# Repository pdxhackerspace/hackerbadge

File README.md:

# PDX Hackerspace Hackerbadge

The unofficial badge of PDX Hackerspace.

- 37 WS2812B addressable RGB LEDs
- SeeedStudio Xiao ESP32-S3 (8MB PSRAM/8MB flash)
- LSM6DSO accelerometer/gyroscope
- 18650 LiPO battery
- Qwiic/STEMMA QT I2C connector

Though we've specced this for a Xiao ESP32-S3, this should work with any Xiao board with a compatible pinout. If the board doesn't support LiPO battery charging then obviously it will only work when plugged into USB.

## LED power

LEDs are powered either through the VBUS or VBAT, avoiding straining the board's 3.3V regulator and providing more voltage to them for more reliable operation. We use two SS23 Schottky diodes to OR the power sources together and avoid feeding back into one another.

## LED control

Xiao ESP32-S3 D10 controls the LEDs.

## Qwiic/STEMMA QT/I2C

SDA - D1
SCL - D0

## Accelerometer/Gyroscope

The board includes an LSM6DSO accelerometer/gyroscope for fancy effects, or you can just ignore it. I2C address 0x6A.

## Firmware

Hardware self-test sketches live under `firmware/test/`. They cycle LED colors/patterns and exercise the LSM6DSO. Production-style options (WLED, ESPHome, CircuitPython) are below.

### WLED

1. Hold the Xiao **BOOT** button, plug in USB, then release BOOT so the board is in download mode.
2. Open the [WLED web installer](https://install.wled.me/) (or [alternate installer](https://wled-install.github.io/)) in Chrome/Edge.
3. Choose an **ESP32-S3** build that matches this board: **8MB flash** and **PSRAM** (OPI / `qio_opi` style binaries are the usual fit for the Xiao ESP32-S3). Flash it.
4. Join Wi‑Fi AP `WLED-AP` (password `wled1234`) and open [http://4.3.2.1](http://4.3.2.1).
5. **Config → LED Preferences** and set:
   - LED count / length: **37**
   - GPIO / data pin: **9** (Xiao **D10**)
   - LED type: **WS281x**
   - Color order: **GRB**
6. Save, then optionally configure your home Wi‑Fi under **Config → WiFi Setup**.

Stock WLED does not use the LSM6DSO.

**Docker Compose** (build a badge-tuned binary with GPIO 9 / 37 LEDs preconfigured):

```bash
cd firmware/wled
docker compose run --rm build
```

Firmware ends up under `firmware/wled/build/`. Flash with the web installer, `esptool`, or:

```bash
DEVICE=/dev/ttyACM0 docker compose run --rm --device=$DEVICE build upload
```

If the OPI-PSRAM build won’t boot, try `PIO_ENV=hackerbadge_qspi docker compose run --rm build`. See also [Compiling WLED](https://kno.wled.ge/advanced/compiling-wled/).

### ESPHome

Test config: `firmware/test/esphome/badge_test.yaml`

Requires an ESPHome release with the `motion` / `lsm6ds` platform. After flash, the badge cycles LED effects and logs IMU samples over serial. It also brings up AP `Hackerbadge-Test` (password `hackerspace`); open [http://192.168.4.1](http://192.168.4.1) for the web UI.

**Docker Compose** (dashboard on [http://localhost:6052](http://localhost:6052)):

```bash
cd firmware/test/esphome
docker compose up
```

Compile only, or compile and flash over USB:

```bash
docker compose run --rm esphome compile badge_test.yaml
DEVICE=/dev/ttyACM0 docker compose run --rm --device=$DEVICE esphome run badge_test.yaml
```

Without Docker: `esphome run firmware/test/esphome/badge_test.yaml`

### CircuitPython

Test program: `firmware/test/circuitpython/code.py`

1. Install [CircuitPython for Seeed Xiao ESP32-S3](https://circuitpython.org/board/seeed_xiao_esp32s3/).
2. From the [Adafruit library bundle](https://circuitpython.org/libraries), copy into `CIRCUITPY/lib/`:
   - `neopixel.mpy` (and `adafruit_pixelbuf.mpy` if present in your bundle)
   - `adafruit_lsm6ds/`
   - `adafruit_bus_device/`
   - `adafruit_register/`
3. Copy `firmware/test/circuitpython/code.py` to `CIRCUITPY/code.py`.

Watch the serial REPL for IMU logs while LEDs cycle.

### Arduino

Test sketch: `firmware/test/arduino/badge_test/badge_test.ino`

**Docker Compose** (Arduino CLI build; artifacts in `firmware/test/arduino/build/`):

```bash
cd firmware/test/arduino
docker compose run --rm build
```

Upload over USB after a successful compile:

```bash
DEVICE=/dev/ttyACM0 docker compose run --rm --device=$DEVICE build upload
```

Without Docker:

1. In Arduino IDE, install board support for **Seeed XIAO ESP32S3**.
2. Install libraries: **FastLED**, **Adafruit LSM6DS** (pulls in BusIO and Unified Sensor).
3. Open the `badge_test` sketch, select the Xiao ESP32S3 board/port, and upload.

Serial Monitor at 115200 baud shows effect names and IMU readings.

## Assembly

The badge comes prebuilt except for the Xiao and the battery holder, which are mounted on the back of the board. We suggest soldering on the Xiao using solder paste and a hot air gun. You're unlikely to make a solder plate work due to the components on the front of the board. The most difficult part will be the battery connectors under the board.

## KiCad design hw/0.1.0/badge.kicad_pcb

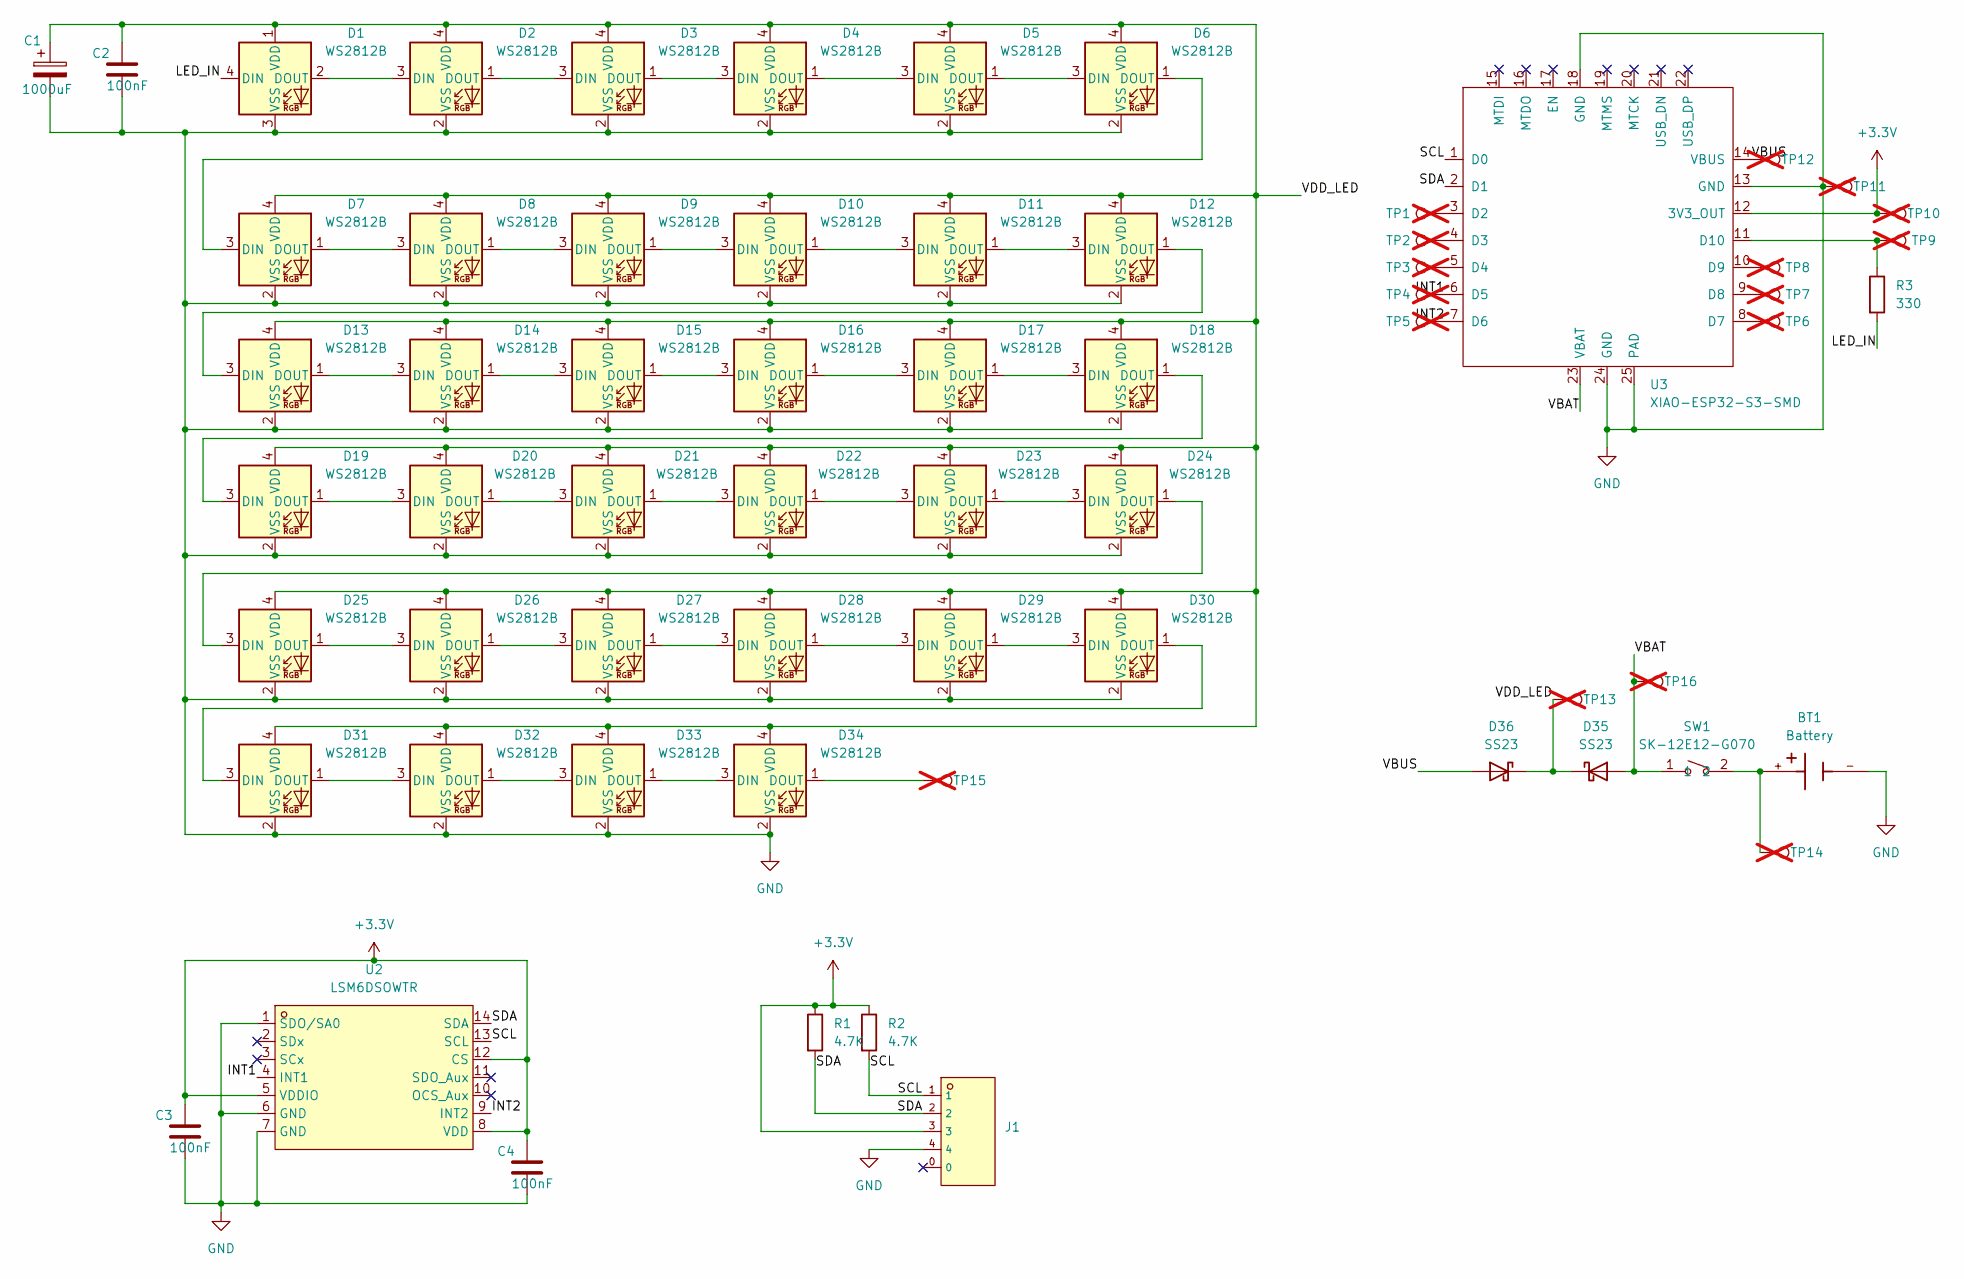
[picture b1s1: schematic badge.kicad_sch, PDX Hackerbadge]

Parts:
BT1: Battery; BAT_BK-18650-PC2; PARTREV F
C1: 1000uF; CP_Elec_5x5.4; MPN C3337
C2, C3, C4: 100nF; C_0402_1005Metric_Pad0.74x0.62mm_HandSolder; MPN C1523
D1, D2, D3, D4, D5, D6, D7, D8, D9, D10, D11, D12, D13, D14, D15, D16, D17, D18, D19, D20, D21, D22, D23, D24, D25, D26, D27, D28, D29, D30, D31, D32, D33, D34: WS2812B; LED_WS2812B_PLCC4_5.0x5.0mm_P3.2mm; MPN C52917433
D35, D36: SS23; D_SMA; MPN C232851
J1: CONN-SMD_4P-P1.00_SM04B-SRSS-TB-LF-SN; MPN C160404; LCSC C160390
R1, R2: 4.7K; R_0805_2012Metric_Pad1.20x1.40mm_HandSolder; MPN C105427
R3: 330; R_0402_1005Metric_Pad0.72x0.64mm_HandSolder; MPN C25104
SW1: SK-12E12-G070; SW-TH_MS-12D08G3.5; LCSC Part C2939255
TP1: D2; TestPoint_Pad_D1.0mm; not fitted
TP2: D3; TestPoint_Pad_D1.0mm; not fitted
TP3: D4; TestPoint_Pad_D1.0mm; not fitted
TP4: D5; TestPoint_Pad_D1.0mm; not fitted
TP5: INT2; TestPoint_Pad_D1.0mm; not fitted
TP6: D7; TestPoint_Pad_D1.0mm; not fitted
TP7: D8; TestPoint_Pad_D1.0mm; not fitted
TP8: D9; TestPoint_Pad_D1.0mm; not fitted
TP9: D10; TestPoint_Pad_D1.0mm; not fitted
TP10: 3V3; TestPoint_Pad_D1.0mm; not fitted
TP11: GND; TestPoint_Pad_D1.0mm; not fitted
TP12: VBUS; TestPoint_Pad_D1.0mm; not fitted
TP13: VDD_LED; TestPoint_Pad_D1.0mm; not fitted
TP14: RAWBAT; TestPoint_Pad_D1.0mm; not fitted
TP15: D34 DOUT; TestPoint_Pad_D1.0mm; not fitted
TP16: VBAT; TestPoint_Pad_D1.0mm; not fitted
U2: LSM6DSOWTR; LGA-14L_L3.0-W2.5-P0.50-TL; MPN C2829074; LCSC Part C2829074
U3: XIAO-ESP32-S3-SMD

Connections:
+3.3V: C3.1, C4.1, J1.3, R1.1, R2.1, TP10.1 (1_1), U2.5 (VDDIO), U2.8 (VDD), U2.12 (CS), U3.12 (3V3_OUT)
/INT1: TP4.1 (1_1), U2.4 (INT1), U3.6 (D5)
/INT2: TP5.1 (1_1), U2.9 (INT2), U3.7 (D6)
/LED_IN: D1.4 (DIN), R3.2
/SCL: J1.1, R2.2, U2.13 (SCL), U3.1 (D0)
/SDA: J1.2, R1.2, U2.14 (SDA), U3.2 (D1)
/VBAT: D35.2 (A), SW1.1, TP16.1 (1_1), U3.23 (VBAT)
/VBUS: D36.2 (A), TP12.1 (1_1), U3.14 (VBUS)
/VDD_LED: C1.1, C2.1, D1.1 (VDD), D2.4 (VDD), D3.4 (VDD), D4.4 (VDD), D5.4 (VDD), D6.4 (VDD), D7.4 (VDD), D8.4 (VDD), D9.4 (VDD), D10.4 (VDD), D11.4 (VDD), D12.4 (VDD), D13.4 (VDD), D14.4 (VDD), D15.4 (VDD), D16.4 (VDD), D17.4 (VDD), D18.4 (VDD), D19.4 (VDD), D20.4 (VDD), D21.4 (VDD), D22.4 (VDD), D23.4 (VDD), D24.4 (VDD), D25.4 (VDD), D26.4 (VDD), D27.4 (VDD), D28.4 (VDD), D29.4 (VDD), D30.4 (VDD), D31.4 (VDD), D32.4 (VDD), D33.4 (VDD), D34.4 (VDD), D35.1 (K), D36.1 (K), TP13.1 (1_1)
GND: BT1.-, C1.2, C2.2, C3.2, C4.2, D1.3 (VSS), D2.2 (VSS), D3.2 (VSS), D4.2 (VSS), D5.2 (VSS), D6.2 (VSS), D7.2 (VSS), D8.2 (VSS), D9.2 (VSS), D10.2 (VSS), D11.2 (VSS), D12.2 (VSS), D13.2 (VSS), D14.2 (VSS), D15.2 (VSS), D16.2 (VSS), D17.2 (VSS), D18.2 (VSS), D19.2 (VSS), D20.2 (VSS), D21.2 (VSS), D22.2 (VSS), D23.2 (VSS), D24.2 (VSS), D25.2 (VSS), D26.2 (VSS), D27.2 (VSS), D28.2 (VSS), D29.2 (VSS), D30.2 (VSS), D31.2 (VSS), D32.2 (VSS), D33.2 (VSS), D34.2 (VSS), J1.4, TP11.1 (1_1), U2.1 (SDO/SA0), U2.6 (GND), U2.7 (GND), U3.13 (GND), U3.18 (GND), U3.24 (GND), U3.25 (PAD)
unnamed: BT1.+, SW1.2, TP14.1 (1_1)
unnamed: D1.2 (DOUT), D2.3 (DIN)
unnamed: D2.1 (DOUT), D3.3 (DIN)
unnamed: D3.1 (DOUT), D4.3 (DIN)
unnamed: D4.1 (DOUT), D5.3 (DIN)
unnamed: D5.1 (DOUT), D6.3 (DIN)
unnamed: D6.1 (DOUT), D7.3 (DIN)
unnamed: D7.1 (DOUT), D8.3 (DIN)
unnamed: D8.1 (DOUT), D9.3 (DIN)
unnamed: D9.1 (DOUT), D10.3 (DIN)
unnamed: D10.1 (DOUT), D11.3 (DIN)
unnamed: D11.1 (DOUT), D12.3 (DIN)
unnamed: D12.1 (DOUT), D13.3 (DIN)
unnamed: D13.1 (DOUT), D14.3 (DIN)
unnamed: D14.1 (DOUT), D15.3 (DIN)
unnamed: D15.1 (DOUT), D16.3 (DIN)
unnamed: D16.1 (DOUT), D17.3 (DIN)
unnamed: D17.1 (DOUT), D18.3 (DIN)
unnamed: D18.1 (DOUT), D19.3 (DIN)
unnamed: D19.1 (DOUT), D20.3 (DIN)
unnamed: D20.1 (DOUT), D21.3 (DIN)
unnamed: D21.1 (DOUT), D22.3 (DIN)
unnamed: D22.1 (DOUT), D23.3 (DIN)
unnamed: D23.1 (DOUT), D24.3 (DIN)
unnamed: D24.1 (DOUT), D25.3 (DIN)
unnamed: D25.1 (DOUT), D26.3 (DIN)
unnamed: D26.1 (DOUT), D27.3 (DIN)
unnamed: D27.1 (DOUT), D28.3 (DIN)
unnamed: D28.1 (DOUT), D29.3 (DIN)
unnamed: D29.1 (DOUT), D30.3 (DIN)
unnamed: D30.1 (DOUT), D31.3 (DIN)
unnamed: D31.1 (DOUT), D32.3 (DIN)
unnamed: D32.1 (DOUT), D33.3 (DIN)
unnamed: D33.1 (DOUT), D34.3 (DIN)
unnamed: D34.1 (DOUT), TP15.1 (1_1)
unnamed: TP1.1 (1_1), U3.3 (D2)
unnamed: TP2.1 (1_1), U3.4 (D3)
unnamed: TP3.1 (1_1), U3.5 (D4)
unnamed: TP6.1 (1_1), U3.8 (D7)
unnamed: TP7.1 (1_1), U3.9 (D8)
unnamed: TP8.1 (1_1), U3.10 (D9)
unnamed: R3.1, TP9.1 (1_1), U3.11 (D10)

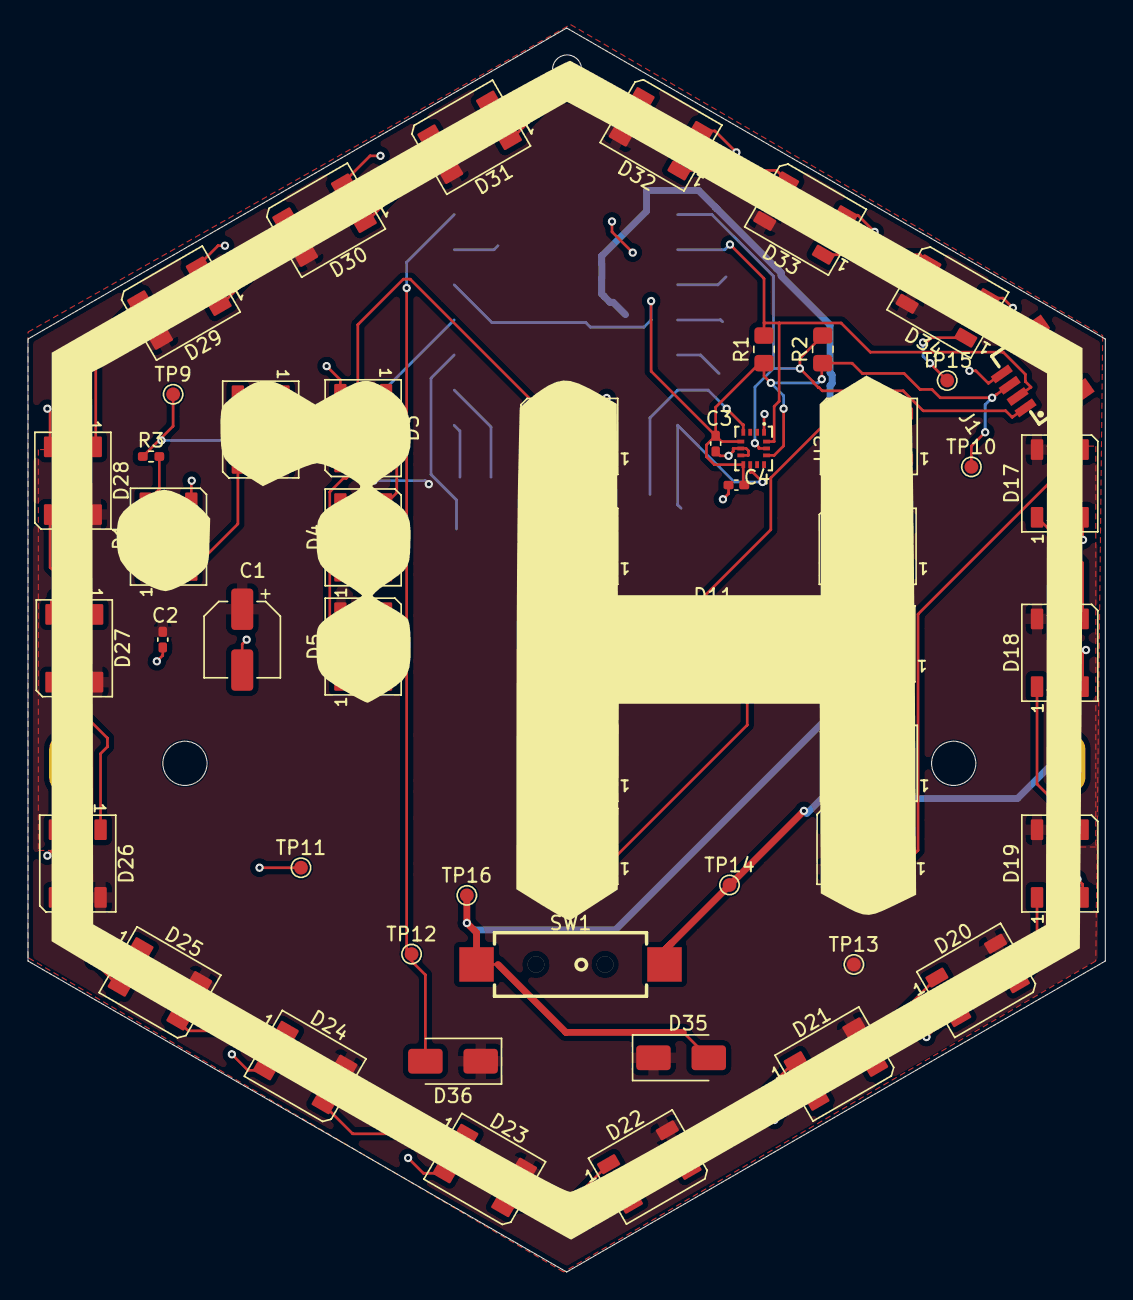
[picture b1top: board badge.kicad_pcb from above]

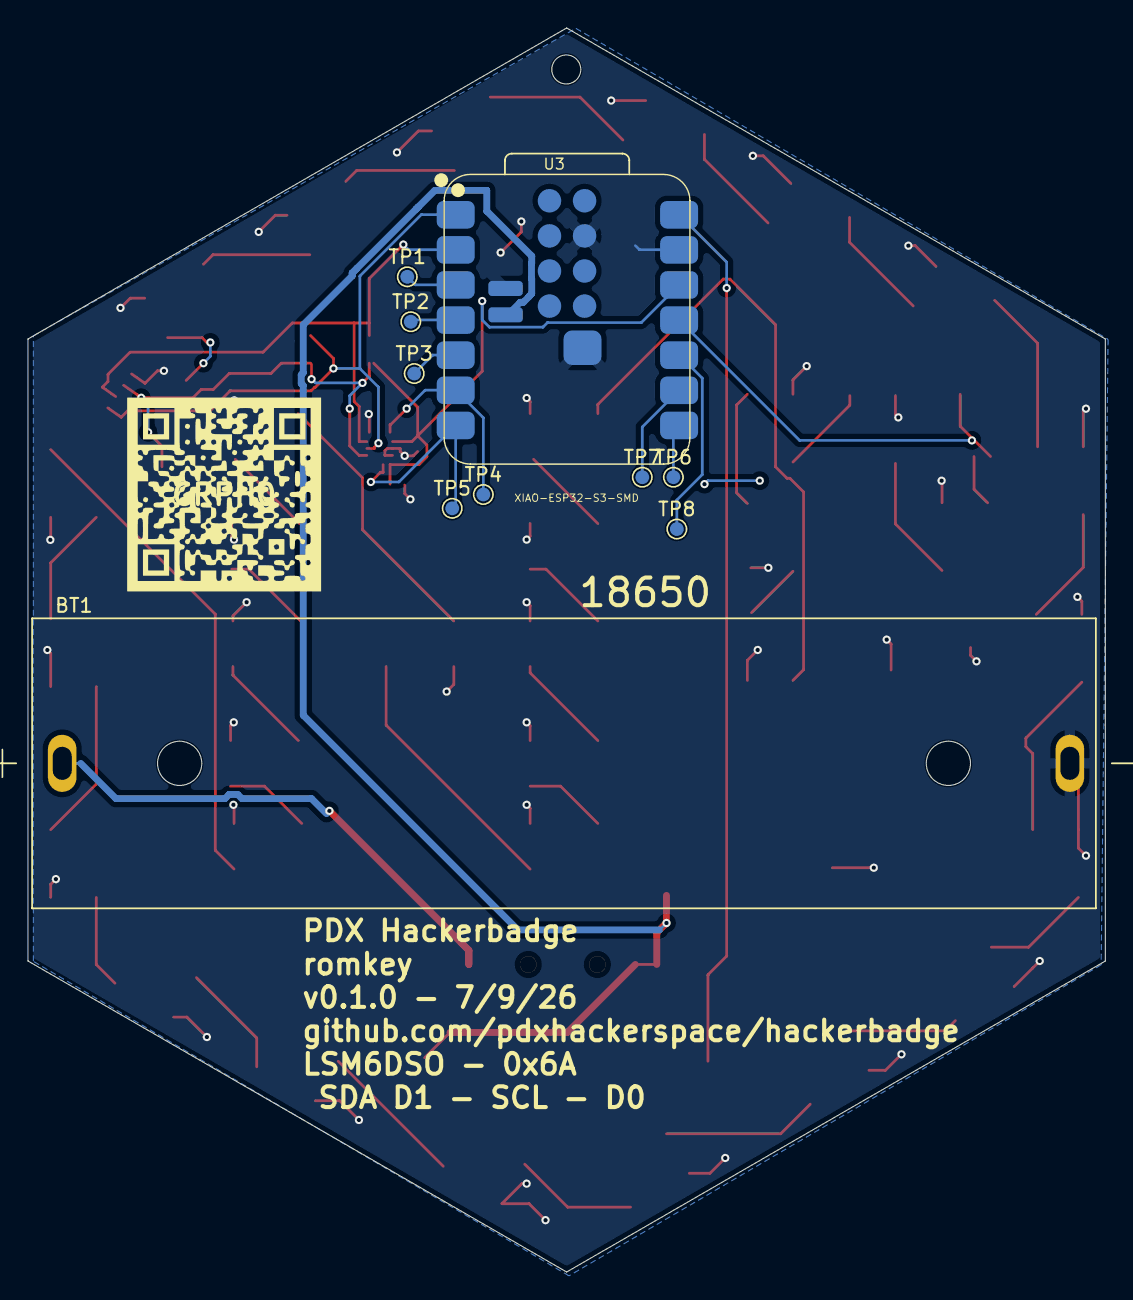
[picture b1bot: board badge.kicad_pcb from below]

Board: 2 copper layers, 77.9 x 90.0 mm, 66 parts (11 on the bottom side), 52 nets.

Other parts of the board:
GRPH0: LOGO
MNT0: MountingHole_2.1mm
